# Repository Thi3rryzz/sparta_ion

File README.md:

Open Source Sparta ION
=============
There's a bunch of (Dutch) blog posts that go with this: (http://infant.tweakblogs.net/blog/cat/2875) (Awesome work InfantEudora)
Also check out the Discord: (https://discord.gg/anZees2)

This repository contains the following:

 folder       |  descr
--------------|-------------------------------------------------------------
 eagle        | All relevant eagle files, BOM lists.
 ion_firmware | AVR Studio projects for the different kinds of firmware.
 ion_software | Software for testing, or uploading hex files.
 lib          | Files used in either firmware or software.
 lib_ion      | Files used for Sparta ION specific code.

All files in this repository are released under GNU GPLv3 (https://www.gnu.org/copyleft/gpl.html)

Software used:
----------------
 - Atmel Studio 7.0.2397 (https://www.microchip.com/mplab/avr-support/atmel-studio-7)
 - GCC 9.3.0
 - Windows: Cygwin(https://cygwin.com/install.html)
 - Eagle 8.6.3 (http://www.cadsoftusa.com/)

Firmware:
----------------

The firmware running your bike's motor, consists of three parts:
 - A bootloader, started on powerup.
 - The actual firmware, called application executed by the bootloader.
 - Configuration memory, stored in ROM.

The bootloader uses two blocks to identify the harware it's running on, and what firmware should be loaded.
The firware uses one block to read/write settings, which are currently the strain gauge calibration.

If you wan't to build a control PCB, use the latest revision of 3phasecntrl.

New Hardare Revision Wishlist:
Motor Driver:
 - Modify 3phasecntrl for XHP motors.
BMS:
 - Modifiy BMS for Li-Ion/Li-Po support.

New Software Revision Wishlist:
 - Enhance CU3 Display support
 - Write BMS code
 - Modify Bootloader for BMS

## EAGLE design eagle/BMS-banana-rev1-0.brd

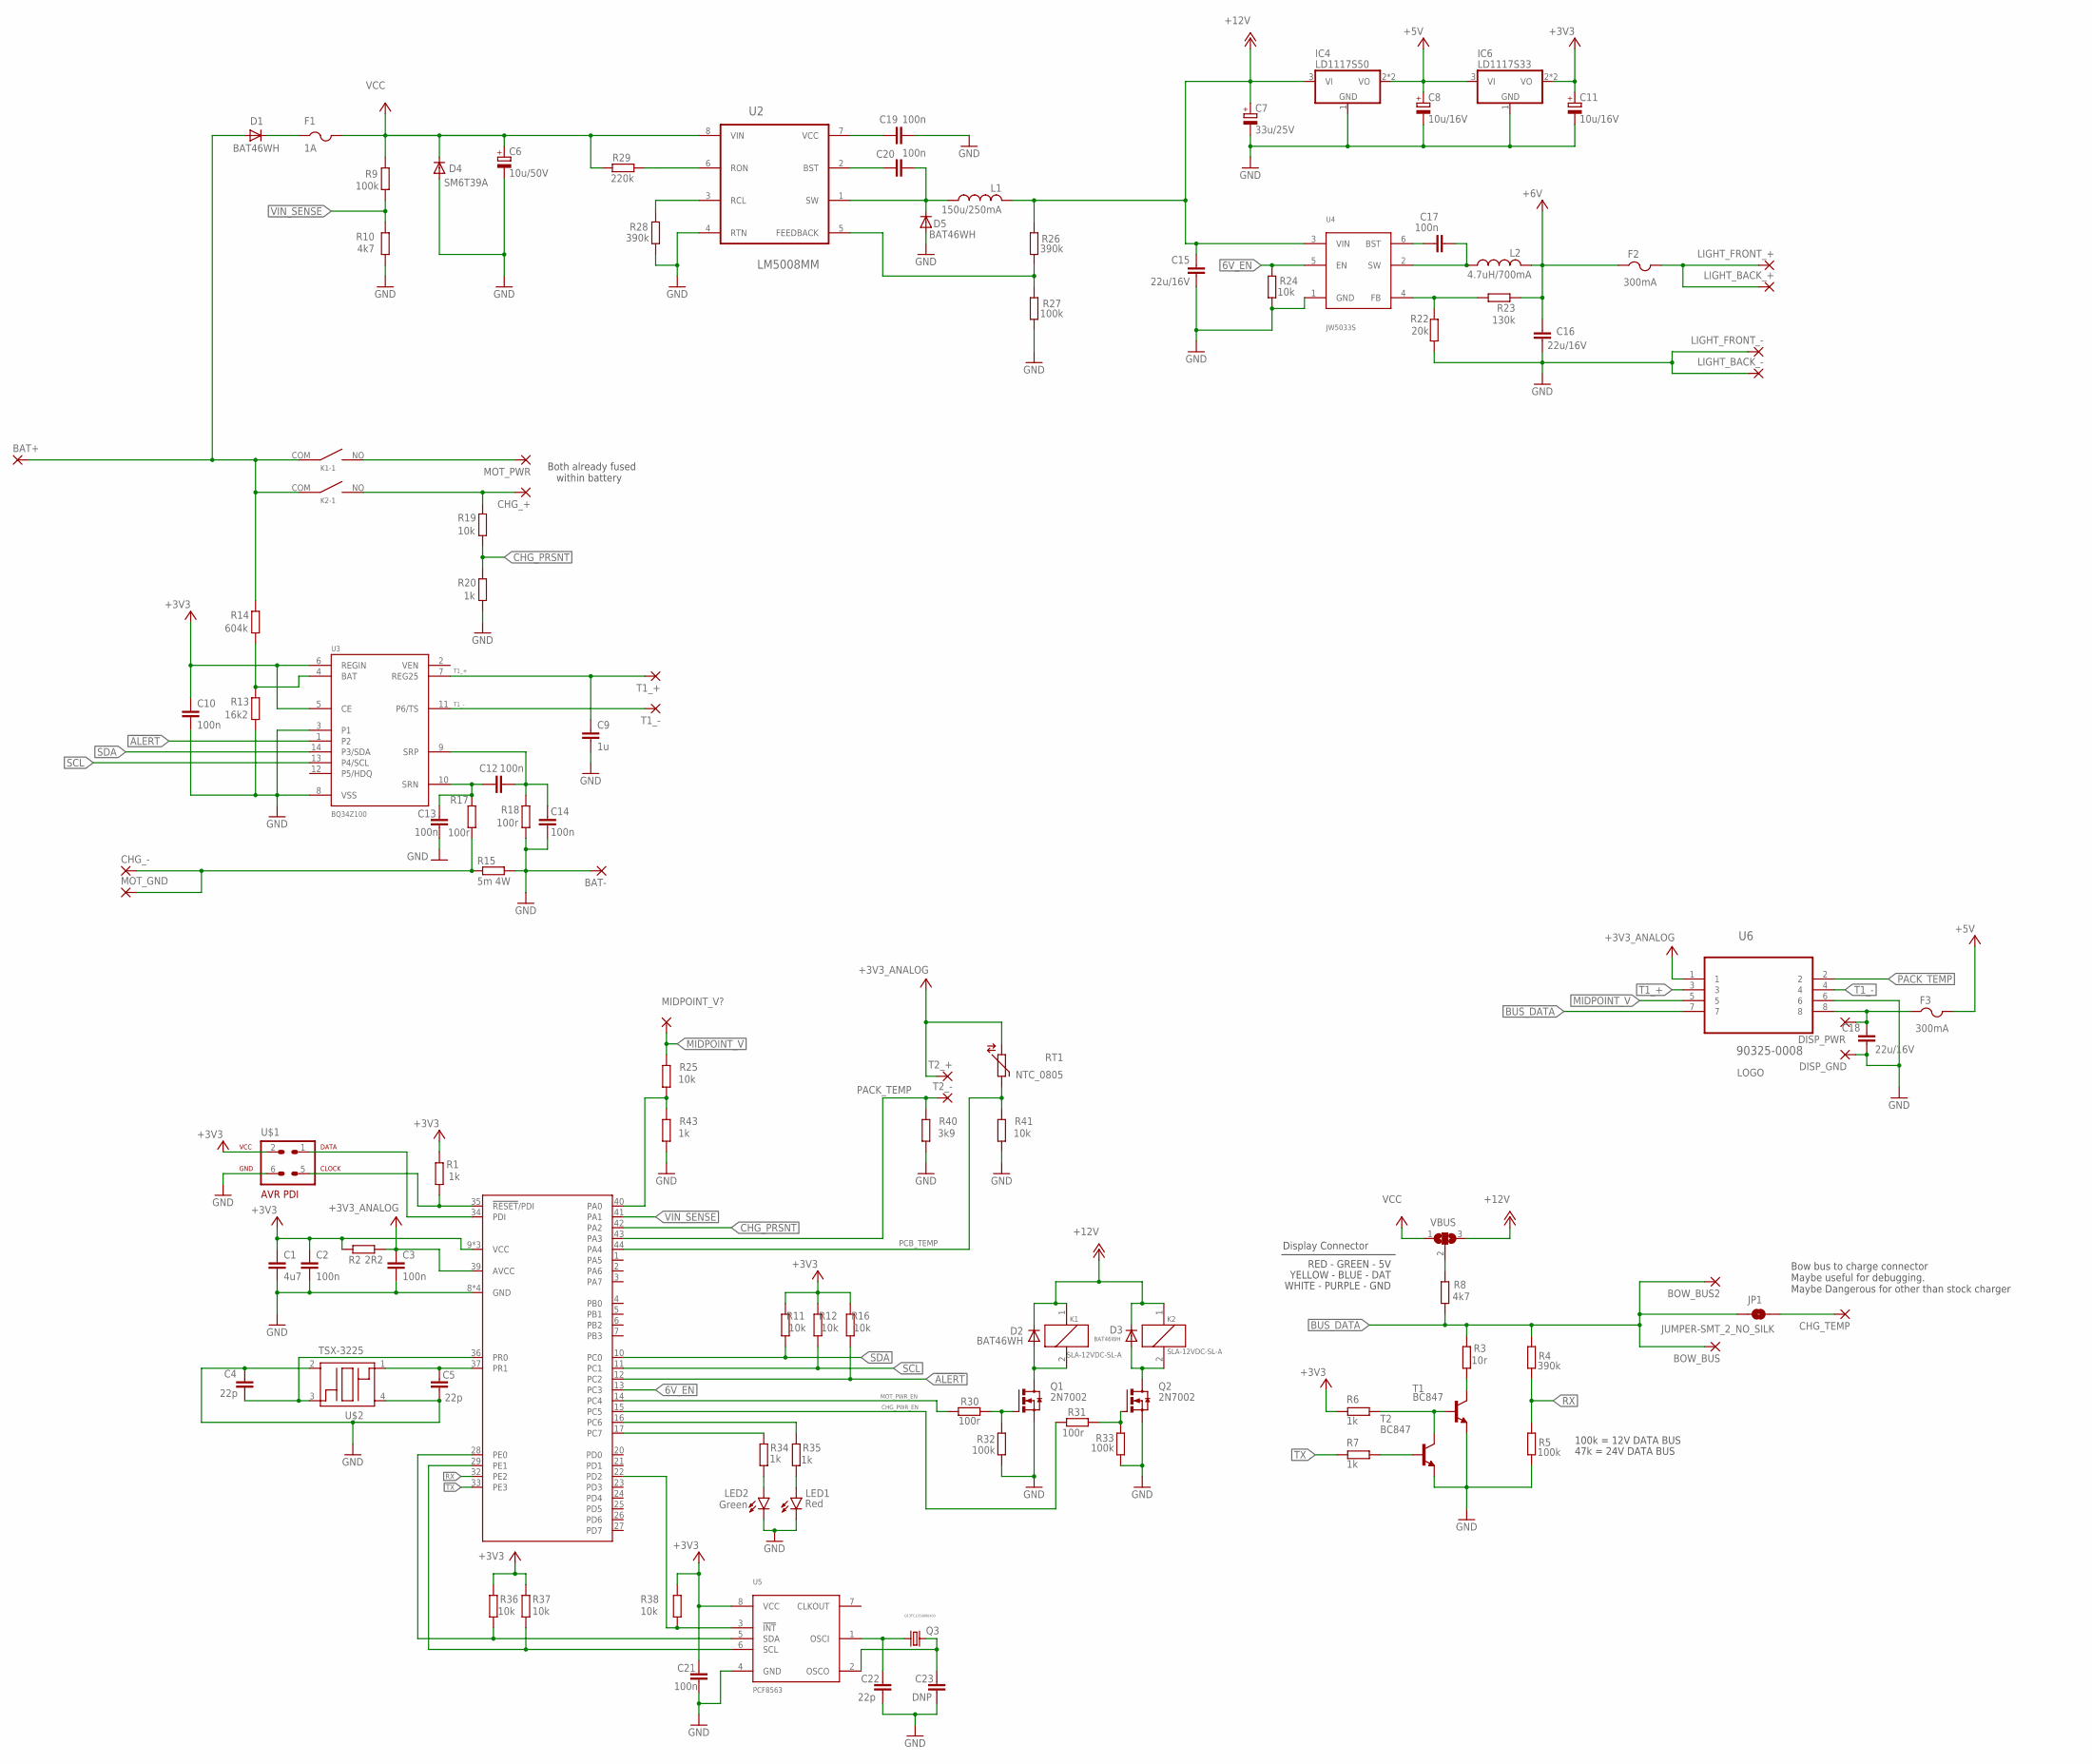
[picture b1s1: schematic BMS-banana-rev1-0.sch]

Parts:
BAT+: 3,81/2,1
BAT-: 3,81/2,1
BOW_BUS: 3,81/2,1
BOW_BUS2: 2,54/0,8
C1: 4u7; C0805
C2, C3, C10, C12, C13, C14, C17, C19, C20, C21: 100n; C0805
C4, C5, C22: 22p; C0805
C6: 10u/50V; 153CLV-0605
C7: 33u/25V; 153CLV-0605
C8, C11: 10u/16V; 153CLV-0405
C9: 1u; C0805
C15, C16, C18: 22u/16V; C0805
C23: DNP; C0805
CHG_+: 3,81/2,1
CHG_-: 3,81/2,1
CHG_TEMP: 3,81/2,1
D1, D2, D3: BAT46WH; SMB; FARNELL 2069340
D4: SM6T39A; SMB; FARNELL 9802703
D5: BAT46WH; SOD323-W
DISP_GND: 2,54/0,8
DISP_PWR: 2,54/0,8
F1: 1A; 1812
F2, F3: 300mA; 1812
IC4: LD1117S50; SOT223; FARNELL 1467780
IC6: LD1117S33; SOT223
JP1: JUMPER-SMT_2_NO_SILK; SMT-JUMPER_2_NO_SILK
K1, K2: SLA-12VDC-SL-A
L1: 150u/250mA; POWER-CHOKE_WE-TPC
L2: 4.7uH/700mA; L0805
LED1: Red; CHIPLED_0805
LED2: Green; CHIPLED_0805
LIGHT_BACK_+: 2,54/0,8
LIGHT_BACK_-: 2,54/0,8
LIGHT_FRONT_+: 2,54/0,8
LIGHT_FRONT_-: 2,54/0,8
MIDPOINT_V?: 2,54/0,8
MOT_GND: 3,81/2,1
MOT_PWR: 3,81/2,1
Q1, Q2: 2N7002; SOT-23
Q3: Q13FC1350000400; CRYSTAL_3215
R1, R6, R7, R20, R34, R35, R43: 1k; R0805
R2: 2R2; R0805
R3: 10r; R0805
R4, R26, R28: 390k; R0805
R5, R9, R27, R32, R33: 100k; R0805
R8, R10: 4k7; R0805
R11, R12, R16, R19, R24, R25, R36, R37, R38, R41: 10k; R0805
R13: 16k2; R0805
R14: 604k; R0805
R15: 5m 4W; R2728
R17, R18, R30, R31: 100r; R0805
R22: 20k; R0805
R23: 130k; R0805
R29: 220k; R0805
R40: 3k9; R0805
RT1: NTC_0805; R0805
T1, T2: BC847; SOT23
T1_+, T1_-, T2_+, T2_-: 2,54/0,8
U1: ATXMEGA32A4U-AU; TQFP-44A-44
U2: LM5008MM; SOP65P490X109-8N
U3: BQ34Z100; PW_R-PDSO-G14
U4: JW5033S; SOT23-6
U5: PCF8563; SO08
U6: 90325-0008; MOLEX_90325-0008
U$1: AVR-PDIVERT; AVR-ISP-6
U$2: TSX-3225
U$4: AFROBOTICLOGOAFROBOTICLOGO_SMALL; AFROBOTICLOGOSMALL
VBUS: SJ2W; SJ_2

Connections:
6V_EN: R24.2, U1.13 (PC3), U4.5 (EN)
!ALERT: R16.1, U1.12 (PC2), U3.1 (P2)
+3V3: C1.1, C2.1, C10.1, C11.+, C21.2, IC6.2 (VO), IC6.4 (VO), R1.2, R2.2, R6.2, R11.2, R12.2, R16.2, R36.2, R37.2, R38.2, U1.9 (VCC), U1.19 (VCC), U1.31 (VCC), U3.5 (CE), U3.6 (REGIN), U5.8 (VCC), U$1.2
+3V3_ANALOG: C3.1, R2.1, RT1.2, T2_+.1, U1.39 (AVCC), U6.1
+5V: C8.+, F3.2, IC4.2 (VO), IC4.4 (VO), IC6.3 (VI)
+6V: C16.2, F2.1, L2.2, R23.1
+12V: C7.+, C15.2, D2.C, D3.C, IC4.3 (VI), K1.1, K2.1, L1.2, R26.2, U4.3 (VIN), VBUS.3
BUS_DATA: BOW_BUS.1, BOW_BUS2.1, JP1.1, R3.2, R4.2, R8.1, U6.7
CHG_PRSNT: R19.1, R20.2, U1.42 (PA2)
CHG_PWR_EN: R31.1, U1.15 (PC5)
GND: BAT-.1, C1.2, C2.2, C3.2, C4.1, C5.2, C6.-, C7.-, C8.-, C9.2, C10.2, C11.-, C13.1, C14.1, C15.1, C16.1, C18.1, C19.2, C21.1, C22.1, C23.1, D4.A, D5.A, DISP_GND.1, IC4.1 (GND), IC6.1 (GND), LED1.C, LED2.C, LIGHT_BACK_-.1, LIGHT_FRONT_-.1, Q1.2 (S), Q2.2 (S), R5.1, R10.1, R13.1, R15.P$2 (2), R18.1, R20.1, R22.1, R24.1, R27.1, R28.1, R32.2, R33.2, R40.1, R41.1, R43.1, T1.2 (E), T2.2 (E), U1.8 (GND), U1.18 (GND), U1.30 (GND), U1.38 (GND), U2.4 (RTN), U3.3 (P1), U3.8 (VSS), U4.1 (GND), U5.4 (GND), U6.6, U$1.6, U$2.2 (GND_2), U$2.4 (GND_4)
MIDPOINT_V: MIDPOINT_V?.1, R25.2, U6.5
MOT_PWR_EN: R30.2, U1.14 (PC4)
unnamed: R1.1, U1.35 (!RESET!/PDI), U$1.5
unnamed: U1.34 (PDI), U$1.1
unnamed: D1.C, F1.1
unnamed: C5.1, U1.37 (PR1), U$2.1 (XTALIN)
unnamed: C4.2, U1.36 (PR0), U$2.3 (XTALOUT)
unnamed: R8.2, VBUS.2
unnamed: C19.1, U2.7 (VCC)
unnamed: R13.2, R14.1, U3.4 (BAT)
unnamed: R22.2, R23.2, U4.4 (FB)
unnamed: CHG_-.1, MOT_GND.1, R15.P$1 (1), R17.1
unnamed: R3.1, T1.3 (C)
unnamed: C12.1, C13.2, R17.2, U3.10 (SRN)
unnamed: CHG_+.1, K2.NO, R19.2
unnamed: C12.2, C14.2, R18.2, U3.9 (SRP)
unnamed: C20.1, U2.2 (BST)
unnamed: K1.NO, MOT_PWR.1
unnamed: CHG_TEMP.1, JP1.2
unnamed: F2.2, LIGHT_BACK_+.1, LIGHT_FRONT_+.1
unnamed: C18.2, DISP_PWR.1, F3.1, U6.8
unnamed: C20.2, D5.C, L1.1, U2.1 (SW)
unnamed: R7.1, T2.1 (B)
unnamed: R26.1, R27.2, U2.5 (FEEDBACK)
unnamed: R6.1, T1.1 (B), T2.3 (C)
unnamed: C17.1, U4.6 (BST)
unnamed: R28.2, U2.3 (RCL)
unnamed: C17.2, L2.1, U4.2 (SW)
unnamed: R25.1, R43.2, U1.40 (PA0)
unnamed: R29.1, U2.6 (RON)
unnamed: Q1.1 (G), R30.1, R32.1
unnamed: D2.A, K1.2, Q1.3 (D)
unnamed: R38.1, U1.22 (PD2), U5.3 (!INT)
unnamed: D3.A, K2.2, Q2.3 (D)
unnamed: Q2.1 (G), R31.2, R33.1
unnamed: LED2.A, R34.1
unnamed: R37.1, U1.29 (PE1), U5.6 (SCL)
unnamed: LED1.A, R35.1
unnamed: R35.2, U1.16 (PC6)
unnamed: R34.2, U1.17 (PC7)
unnamed: R36.1, U1.28 (PE0), U5.5 (SDA)
unnamed: C22.2, Q3.P$1 (1), U5.1 (OSCI)
unnamed: C23.2, Q3.P$2 (2), U5.2 (OSCO)
PACK_TEMP: R40.2, T2_-.1, U1.43 (PA3), U6.2
PCB_TEMP: R41.2, RT1.1, U1.44 (PA4)
RX: R4.1, R5.2, U1.32 (PE2)
SCL: R12.1, U1.11 (PC1), U3.13 (P4/SCL)
SDA: R11.1, U1.10 (PC0), U3.14 (P3/SDA)
T1_+: C9.1, T1_+.1, U3.7 (REG25), U6.3
T1_-: T1_-.1, U3.11 (P6/TS), U6.4
TX: R7.2, U1.33 (PE3)
VBAT: BAT+.1, D1.A, K1.COM, K2.COM, R14.2
VCC: C6.+, D4.C, F1.2, R9.2, R29.2, U2.8 (VIN), VBUS.1
VIN_SENSE: R9.1, R10.2, U1.41 (PA1)

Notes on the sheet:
RED - GREEN - 5V
WHITE - PURPLE - GND
YELLOW - BLUE - DAT
Display Connector
100k = 12V DATA BUS
47k = 24V DATA BUS
Both already fused within battery
Bow bus to charge connector Maybe useful for debugging. Maybe Dangerous for other than stock charger

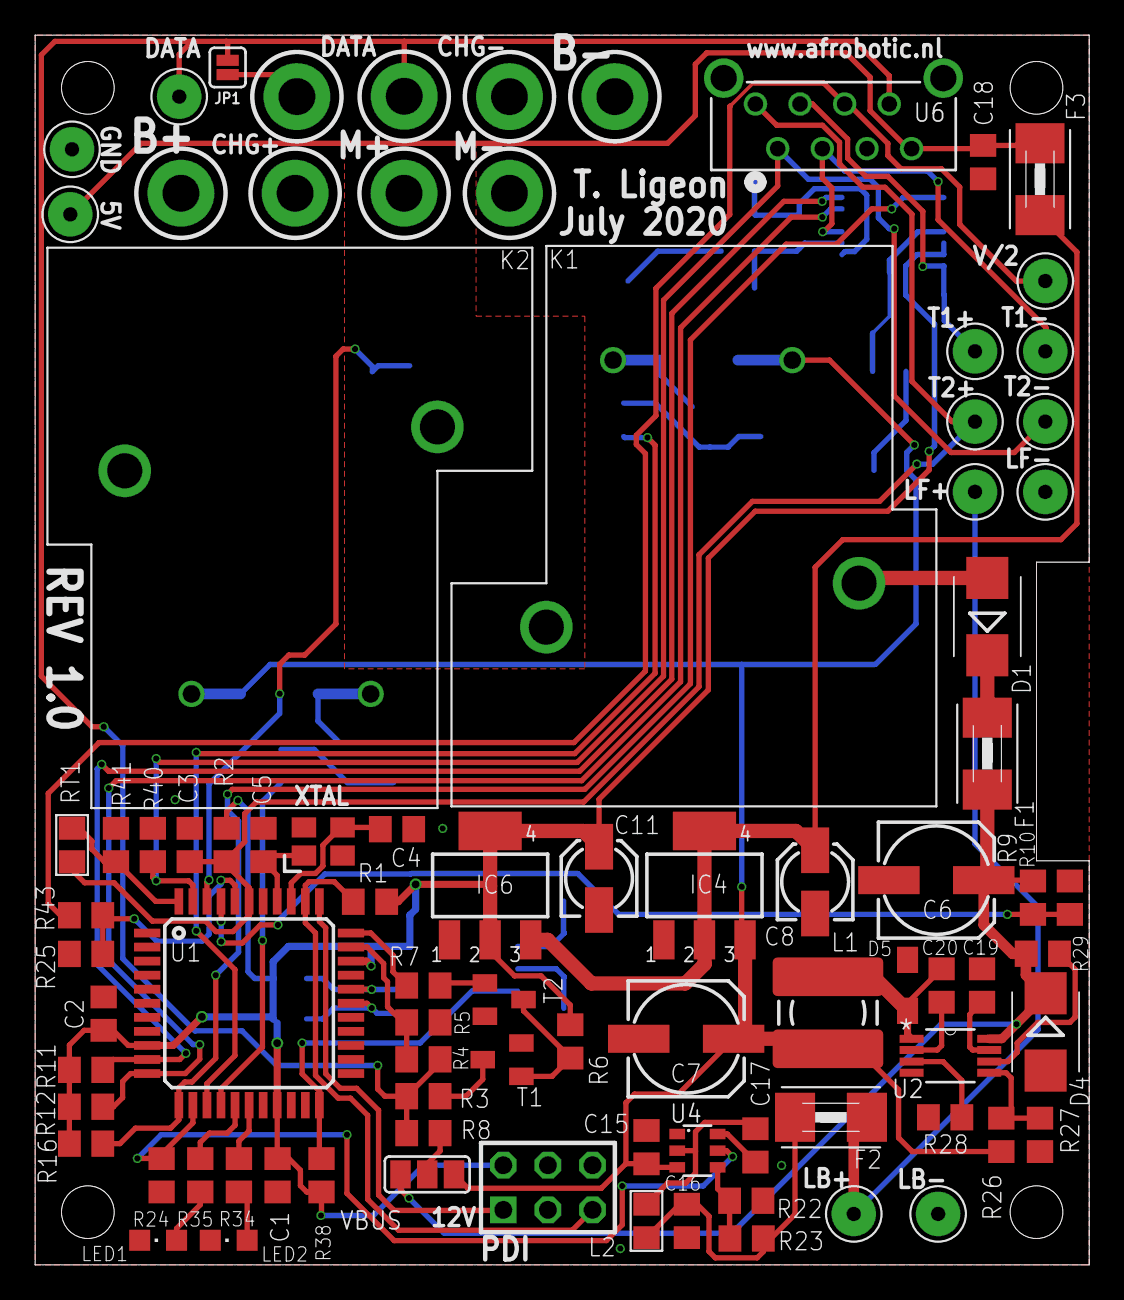
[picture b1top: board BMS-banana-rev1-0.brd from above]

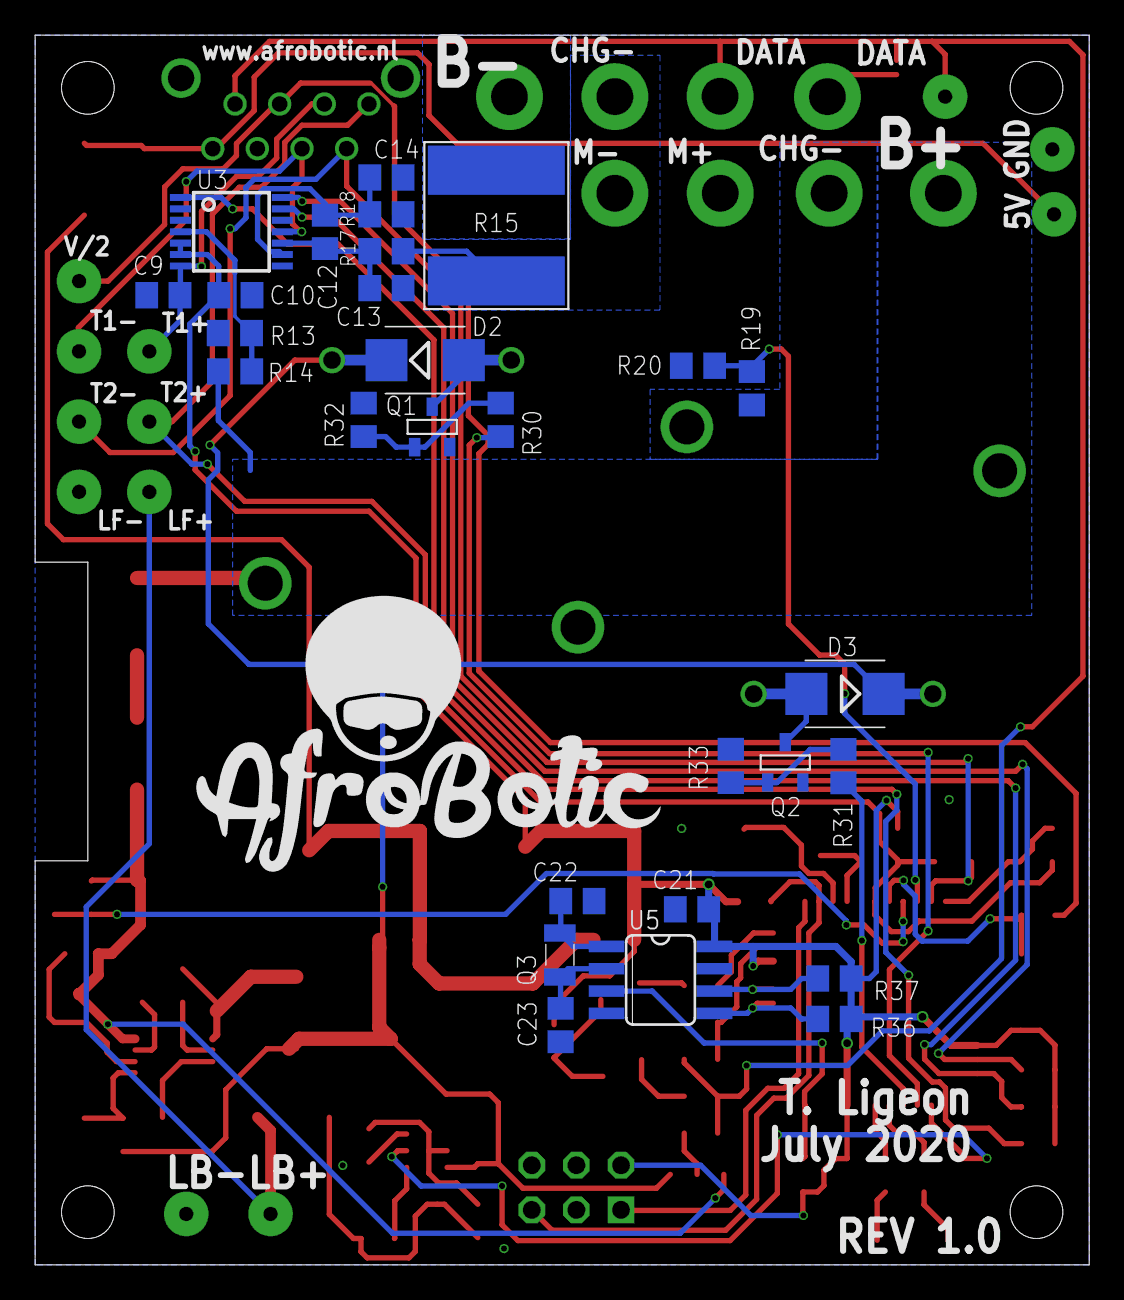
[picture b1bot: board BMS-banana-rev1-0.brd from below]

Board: 2 copper layers, 60.0 x 70.0 mm, 116 parts (29 on the bottom side), 65 nets.

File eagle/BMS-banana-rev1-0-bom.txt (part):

Part          Value                            Device                           Package              Description                             FARNELL LCSC    LSCS   MPN        OC_FARNELL OC_NEWARK PACKAGE               POPULARITY SPICEPREFIX SUPPLIER              
C1            4u7                              C-EUC0805                        C0805                CAPACITOR, European symbol                                                                                           88         C                                 
C2            100n                             C-EUC0805                        C0805                CAPACITOR, European symbol                                                                                           88         C                                 
C3            100n                             C-EUC0805                        C0805                CAPACITOR, European symbol                                                                                           88         C                                 
C4            22p                              C-EUC0805                        C0805                CAPACITOR, European symbol                                                                                           88         C                                 
C5            22p                              C-EUC0805                        C0805                CAPACITOR, European symbol                                                                                           88         C                                 
C6            10u/50V                          CPOL-EU153CLV-0605               153CLV-0605          POLARIZED CAPACITOR, European symbol                                                                                                                              
C7            33u/25V                          CPOL-EU153CLV-0605               153CLV-0605          POLARIZED CAPACITOR, European symbol                                                                                                                              
C8            10u/16V                          CPOL-EU153CLV-0405               153CLV-0405          POLARIZED CAPACITOR, European symbol                                                                                                                              
C9            1u                               C-EUC0805                        C0805                CAPACITOR, European symbol                                                                                           88         C                                 
C10           100n                             C-EUC0805                        C0805                CAPACITOR, European symbol                                                                                           88         C                                 
C11           10u/16V                          CPOL-EU153CLV-0405               153CLV-0405          POLARIZED CAPACITOR, European symbol                                                                                                                              
C12           100n                             C-EUC0805                        C0805                CAPACITOR, European symbol                                                                                           88         C                                 
C13           100n                             C-EUC0805                        C0805                CAPACITOR, European symbol                                                                                           88         C                                 
C14           100n                             C-EUC0805                        C0805                CAPACITOR, European symbol                                                                                           88         C                                 
C15           22u/16V                          C-EUC0805                        C0805                CAPACITOR, European symbol                                                                                           88         C                                 
C16           22u/16V                          C-EUC0805                        C0805                CAPACITOR, European symbol                                                                                           88         C                                 
C17           100n                             C-EUC0805                        C0805                CAPACITOR, European symbol                                                                                           88         C                                 
C18           22u/16V                          C-EUC0805                        C0805                CAPACITOR, European symbol                                                                                           88         C                                 
C19           100n                             C-EUC0805                        C0805                CAPACITOR, European symbol                                                                                           88         C                                 
C20           100n                             C-EUC0805                        C0805                CAPACITOR, European symbol                                                                                           88         C                                 
C21           100n                             C-EUC0805                        C0805                CAPACITOR, European symbol                                                                                           88         C                                 
C22           22p                              C-EUC0805                        C0805                CAPACITOR, European symbol                                                                                           88         C                                 
C23           DNP                              C-EUC0805                        C0805                CAPACITOR, European symbol                                                                                           88         C                                 
D1            BAT46WH                          DIODE-SMB                        SMB                  DIODE                                   2069340                                                                                                                   
D2            BAT46WH                          DIODE-SMB                        SMB                  DIODE                                   2069340                                                                                                                   
D3            BAT46WH                          DIODE-SMB                        SMB                  DIODE                                   2069340                                                                                                                   
D4            SM6T39A                          DIODE-SMB                        SMB                  DIODE                                   9802703                                                                                                                   
D5            BAT46WH                          DIODE-SOD323-W                   SOD323-W             DIODE                                                                                                                                                             
F1            1A                               PTCFUSE-1812                     1812                 PTC fuses, resettable thermistors                                                                                                                                 
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
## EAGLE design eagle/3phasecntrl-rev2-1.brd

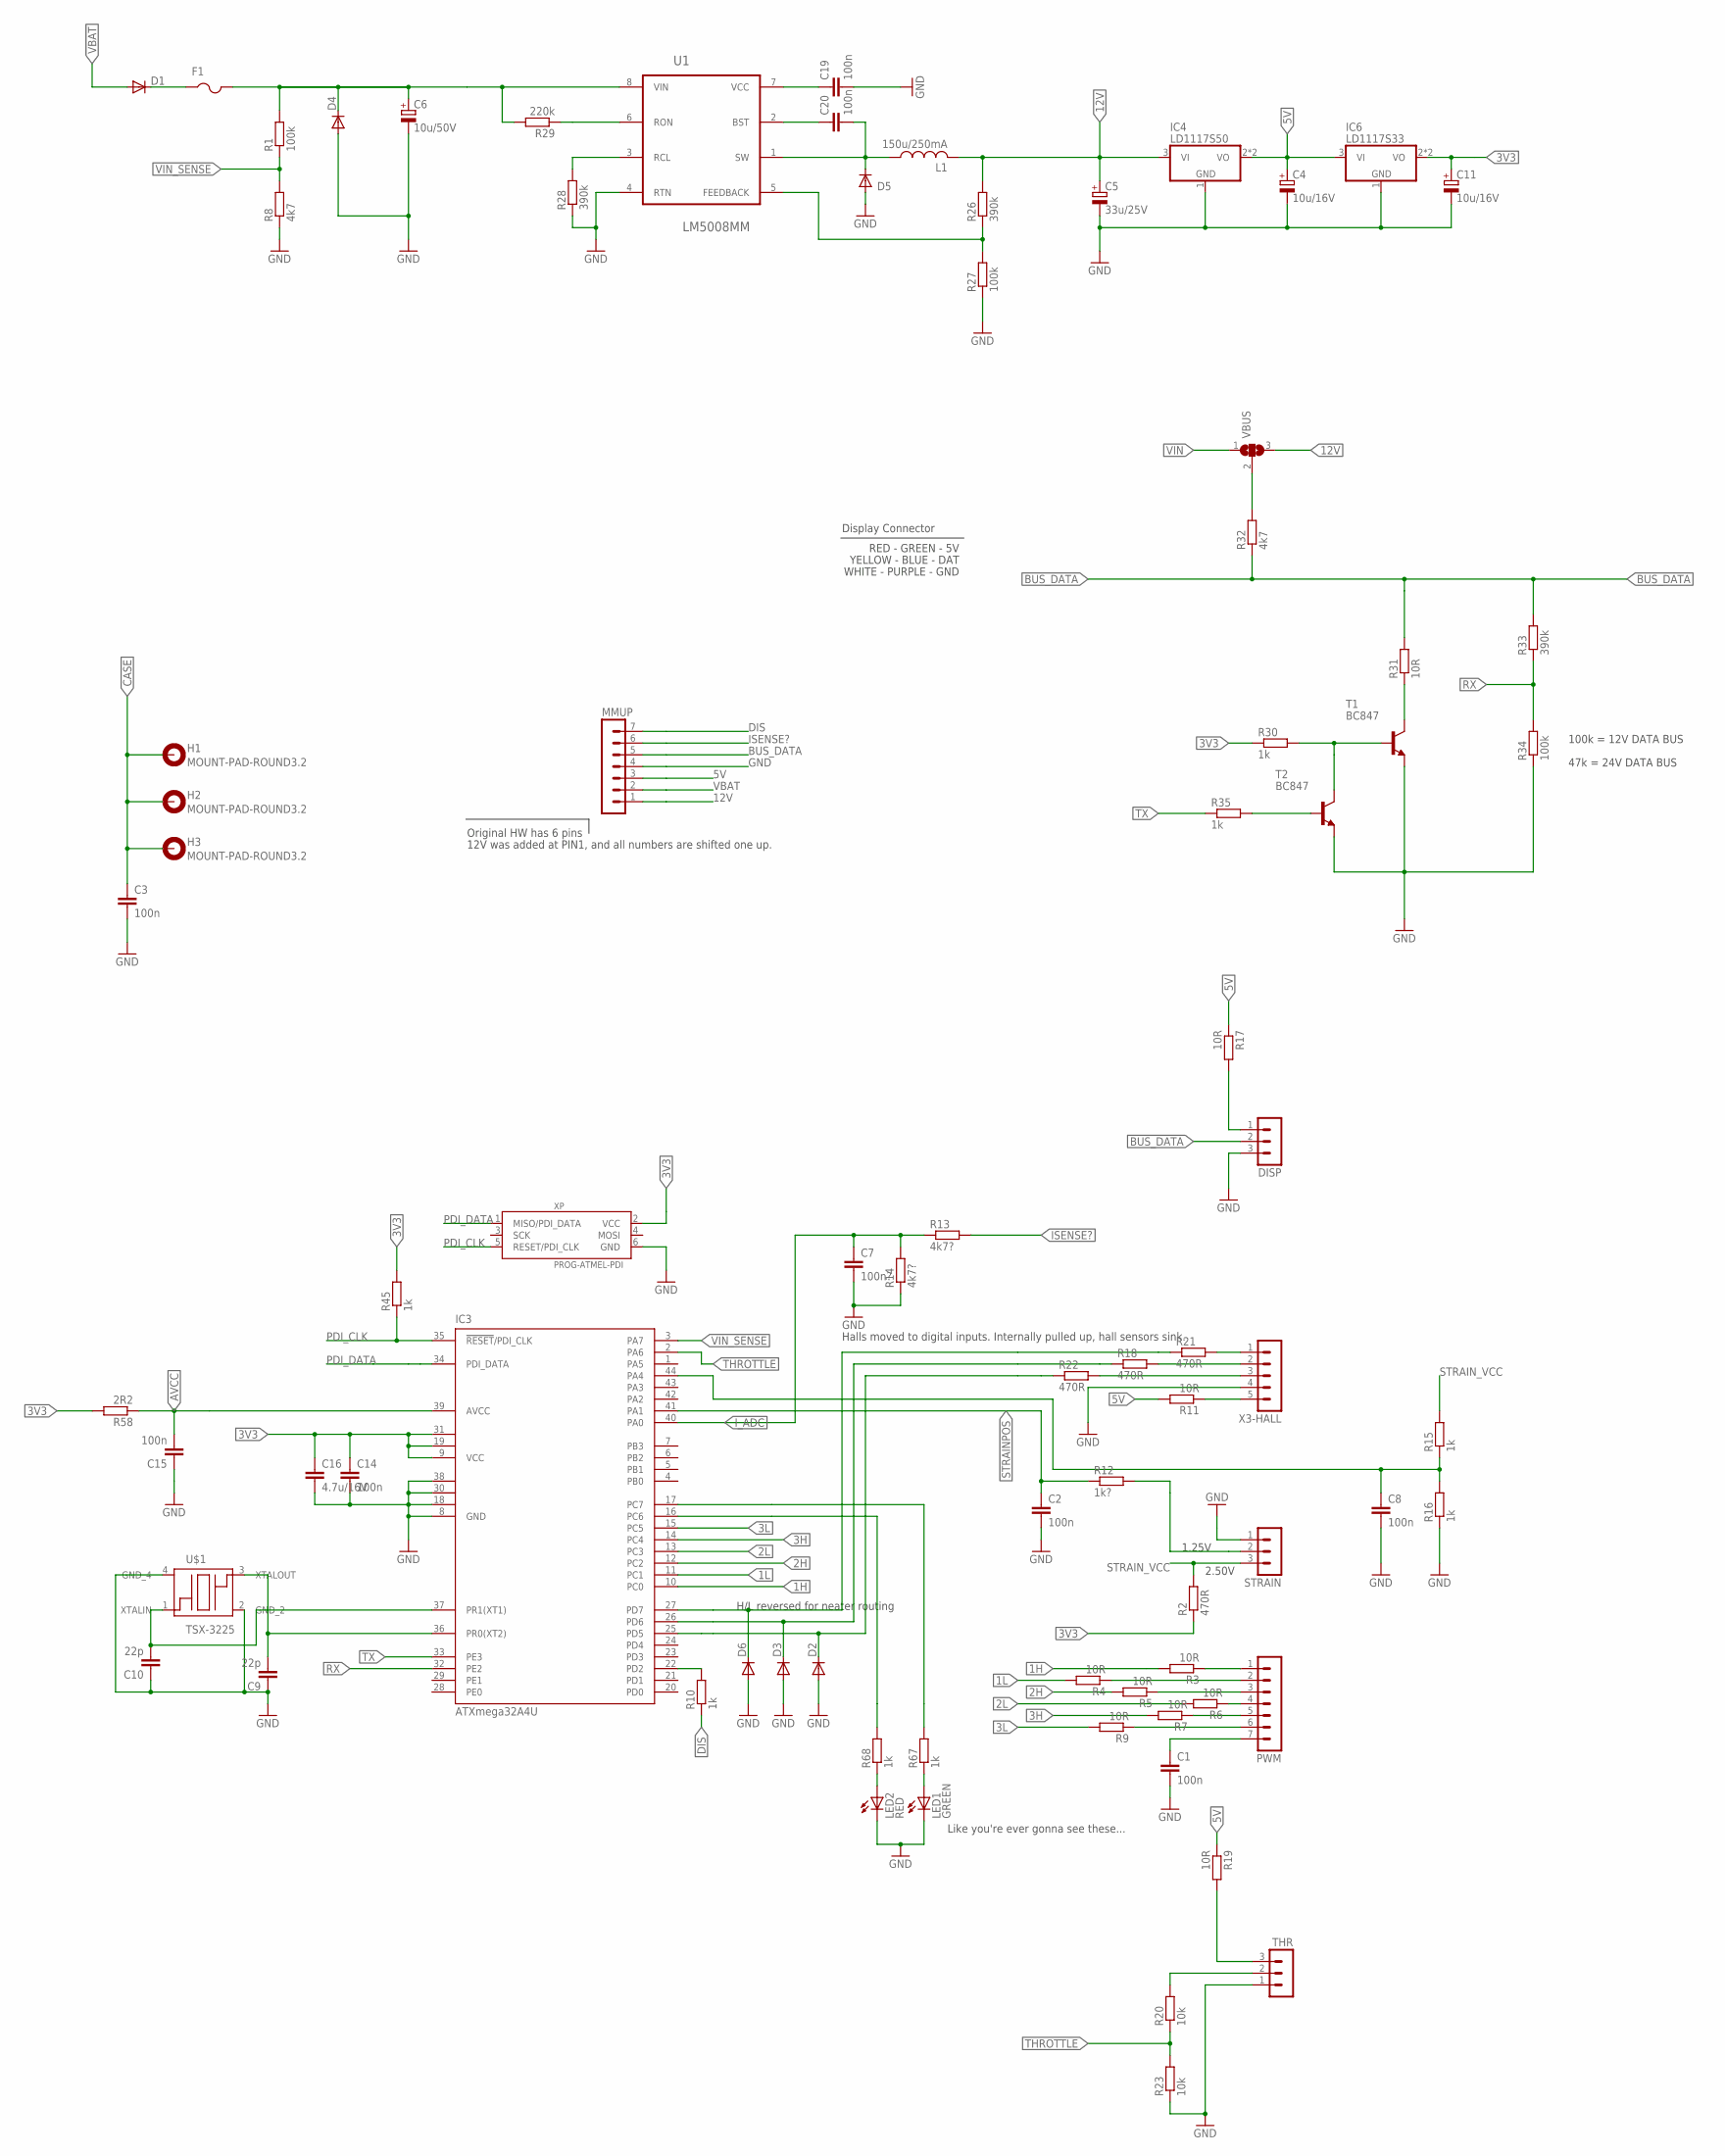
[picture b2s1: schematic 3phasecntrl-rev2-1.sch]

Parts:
C1, C2, C3, C8, C14, C15, C19, C20: 100n; C0805K
C4, C11: 10u/16V; 153CLV-0405
C5: 33u/25V; 153CLV-0605
C6: 10u/50V; 153CLV-0605
C7: 100n?; C0805K
C9, C10: 22p; C0805K
C16: 4.7u/16V; C0805K
D1: BAT46WH; SMB; FARNELL 2069340
D2, D3, D6: PTVS3V3S1UTR; SOD123; FARNELL 2575110
D4: SM6T39A; SMB; FARNELL 9802703
D5: BAT46WH; SOD323-W
DISP: MA03-1
F1: PTCFUSE-1812; 1812
H1, H2, H3: MOUNT-PAD-ROUND3.2; 3,2-PAD
IC3: ATXmega32A4U; TQFP44
IC4: LD1117S50; SOT223; FARNELL 1467780
IC6: LD1117S33; SOT223
L1: 150u/250mA; POWER-CHOKE_WE-TPC
LED1: GREEN; CHIPLED_0805
LED2: RED; CHIPLED_0805
MMUP: MA07-1
PWM: MA07-1
R1, R27, R34: 100k; M0805
R2, R18, R21, R22: 470R; M0805
R3, R4, R5, R6, R7, R9, R11, R17, R19, R31: 10R; M0805
R8, R32: 4k7; M0805
R10, R15, R16, R30, R35, R67, R68: 1k; M0805
R12: 1k?; M0805
R13, R14: 4k7?; M0805
R20, R23: 10k; M0805
R26, R28, R33: 390k; M0805
R29: 220k; M0805
R45: 1k; R0805
R58: 2R2; R0805
STRAIN: MA03-1
T1, T2: BC847; SOT23
THR: MA03-1
U1: LM5008MM; SOP65P490X109-8N
U$1: TSX-3225
VBUS: SJ2W; SJ_2
X3-HALL: MA05-1
XP: PROG-ATMEL-PDI; 6-LSTB2

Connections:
1H: IC3.10 (PC0), R3.2
1L: IC3.11 (PC1), R4.2
2H: IC3.12 (PC2), R5.2
2L: IC3.13 (PC3), R6.2
3H: IC3.14 (PC4), R7.2
3L: IC3.15 (PC5), R9.2
3V3: C11.+, C14.1, C16.1, IC3.9 (VCC), IC3.19 (VCC1), IC3.31 (VCC2), IC6.2 (VO), IC6.4 (VO), R2.1, R30.1, R45.2, R58.2, XP.2 (VCC)
5V: C4.+, IC4.2 (VO), IC4.4 (VO), IC6.3 (VI), MMUP.3, R11.2, R17.1, R19.1
12V: C5.+, IC4.3 (VI), L1.2, MMUP.1, R26.2, VBUS.3
AVCC: C15.2, IC3.39 (AVCC), R58.1
BUS_DATA: DISP.2, MMUP.5, R31.2, R32.1, R33.2
CASE: C3.1, H1.B3,2, H2.B3,2, H3.B3,2
DIS: MMUP.7, R10.1
GND: C1.2, C2.2, C3.2, C4.-, C5.-, C6.-, C7.2, C8.2, C9.1, C10.1, C11.-, C14.2, C15.1, C16.2, C19.2, D2.A, D3.A, D4.A, D5.A, D6.A, DISP.3, IC3.8 (GND), IC3.18 (GND1), IC3.30 (GND2), IC3.38 (GND3), IC4.1 (GND), IC6.1 (GND), LED1.C, LED2.C, MMUP.4, R8.1, R14.1, R16.1, R23.1, R27.1, R28.1, R34.1, STRAIN.1, T1.2 (E), T2.2 (E), THR.1, U1.4 (RTN), U$1.2 (GND_2), U$1.4 (GND_4), X3-HALL.4, XP.6 (GND)
ISENSE?: MMUP.6, R13.2
I_ADC: C7.1, IC3.40 (PA0), R13.1, R14.2
unnamed: C1.1, PWM.7
unnamed: D1.C, F1.1
unnamed: C19.1, U1.7 (VCC)
unnamed: PWM.1, R3.1
unnamed: R12.2, STRAIN.2
unnamed: R32.2, VBUS.2
unnamed: IC3.22 (PD2), R10.2
unnamed: R11.1, X3-HALL.5
unnamed: R21.2, X3-HALL.1
unnamed: PWM.2, R4.1
unnamed: R18.2, X3-HALL.2
unnamed: R31.1, T1.3 (C)
unnamed: R22.2, X3-HALL.3
unnamed: C10.2, IC3.37 (PR1(XT1)), U$1.1 (XTALIN)
unnamed: LED1.A, R67.1
unnamed: LED2.A, R68.1
unnamed: C20.1, U1.2 (BST)
unnamed: R19.2, THR.3
unnamed: D6.C, IC3.27 (PD7), R21.1
unnamed: IC3.16 (PC6), R68.2
unnamed: IC3.17 (PC7), R67.2
unnamed: C20.2, D5.C, L1.1, U1.1 (SW)
unnamed: R35.2, T2.1 (B)
unnamed: R26.1, R27.2, U1.5 (FEEDBACK)
unnamed: R30.2, T1.1 (B), T2.3 (C)
unnamed: D3.C, IC3.26 (PD6), R18.1
unnamed: R28.2, U1.3 (RCL)
unnamed: PWM.3, R5.1
unnamed: PWM.4, R6.1
unnamed: R29.1, U1.6 (RON)
unnamed: D2.C, IC3.25 (PD5), R22.1
unnamed: PWM.5, R7.1
unnamed: PWM.6, R9.1
unnamed: DISP.1, R17.2
unnamed: C9.2, IC3.36 (PR0(XT2)), U$1.3 (XTALOUT)
PDI_CLK: IC3.35 (!RESET!/PDI_CLK), R45.1, XP.5 (RESET/PDI_CLK)
PDI_DATA: IC3.34 (PDI_DATA), XP.1 (MISO/PDI_DATA)
RX: IC3.32 (PE2), R33.1, R34.2
STRAINPOS: C2.1, IC3.41 (PA1), R12.1
STRAINREF: C8.1, IC3.44 (PA4), R15.1, R16.2
STRAIN_VCC: R2.2, R15.2, STRAIN.3
THIN: R20.2, THR.2
THROTTLE: IC3.2 (PA6), R20.1, R23.2
TX: IC3.33 (PE3), R35.1
VBAT: D1.A, MMUP.2
VIN: C6.+, D4.C, F1.2, R1.2, R29.2, U1.8 (VIN), VBUS.1
VIN_SENSE: IC3.3 (PA7), R1.1, R8.2

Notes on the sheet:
RED - GREEN - 5V
WHITE - PURPLE - GND
YELLOW - BLUE - DAT
1.25V
2.50V
Original HW has 6 pins
12V was added at PIN1, and all numbers are shifted one up.
Display Connector
H/L reversed for neater routing
Like you're ever gonna see these...
Halls moved to digital inputs. Internally pulled up, hall sensors sink.
100k = 12V DATA BUS
47k = 24V DATA BUS

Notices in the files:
parts and their libraries:
SparkFun-Jumpers: Licensing: Creative Commons ShareAlike 4.0 International - https://creativecommons.org/licenses/by-sa/4.0
